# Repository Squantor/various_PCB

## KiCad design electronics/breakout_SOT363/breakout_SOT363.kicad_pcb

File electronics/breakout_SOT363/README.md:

# STO363 breakout board
Simple breakout for SOT363 devices
## TODO's
Still some things need to be done:
* Review with one night in between
* Produce at [OSHPARK](https://oshpark.com/)
* Assemble
* Test & characterise
* update Readme.md with pictures and BOM

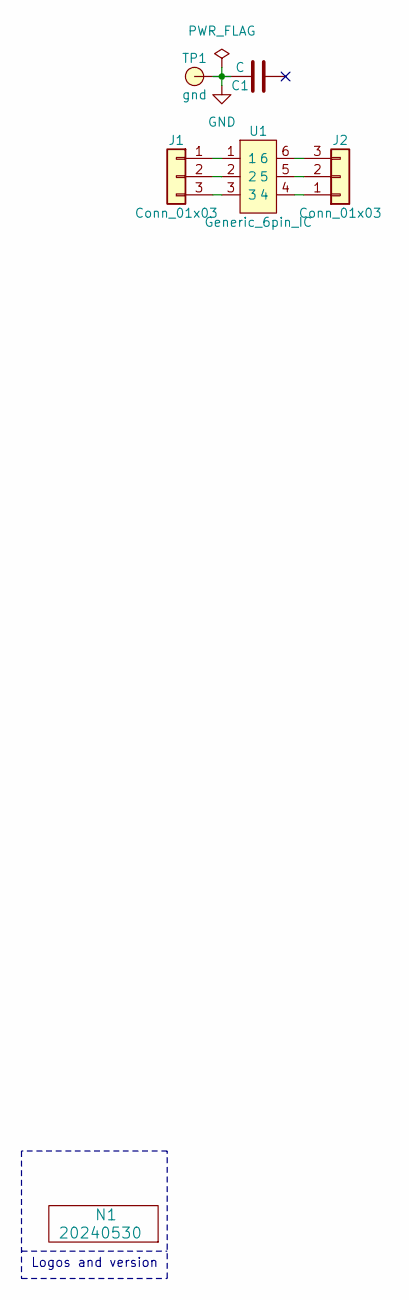
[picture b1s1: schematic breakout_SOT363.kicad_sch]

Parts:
C1: C; C_0805+0603
J1, J2: Conn_01x03; Header-0254-1X03-H010
N1: 20240530; Label_Generic
TP1: gnd; TestPoint_hole_H03R07
U1: Generic_6pin_IC; SOT363-NXP-hand

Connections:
GND: C1.1, TP1.1
unnamed: J1.1, U1.1
unnamed: J1.2, U1.2
unnamed: J1.3, U1.3
unnamed: J2.1, U1.4
unnamed: J2.2, U1.5
unnamed: J2.3, U1.6

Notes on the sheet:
Logos and version

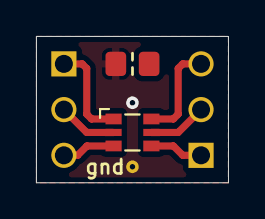
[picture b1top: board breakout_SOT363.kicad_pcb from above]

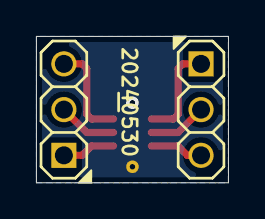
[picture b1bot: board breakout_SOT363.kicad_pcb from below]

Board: 2 copper layers, 10.7 x 8.1 mm, 6 parts (3 on the bottom side), 7 nets.

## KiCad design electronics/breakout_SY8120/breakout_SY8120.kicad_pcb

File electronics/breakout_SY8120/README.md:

# SY8120 breakout board
Breakout for the [SY8120I](https://datasheet.lcsc.com/szlcsc/2001171834_Silergy-Corp-SY8120IABC_C479076.pdf) step down converter, can also be used as a LM7805 replacement.
## TODO's
Still some things need to be done:
* Review with one night in between
* Produce at [OSHPARK](https://oshpark.com/)
* Assemble
* Test & characterise
* update Readme.md with pictures and BOM
## BOM
* [SY8120I](https://lcsc.com/product-detail/DC-DC-Converters_Silergy-Corp-SY8120IABC_C479076.html)
* [Inductor 4.7uH 3.2A](https://lcsc.com/product-detail/Inductors-SMD_TDK-SLF6045T-4R7N2R4-3PF_C93218.html)
* [Capacitor 10uF 25V X7R](https://lcsc.com/product-detail/Multilayer-Ceramic-Capacitors-MLCC-SMD-SMT_Samsung-Electro-Mechanics-CL31B106KAHNNNE_C14860.html)

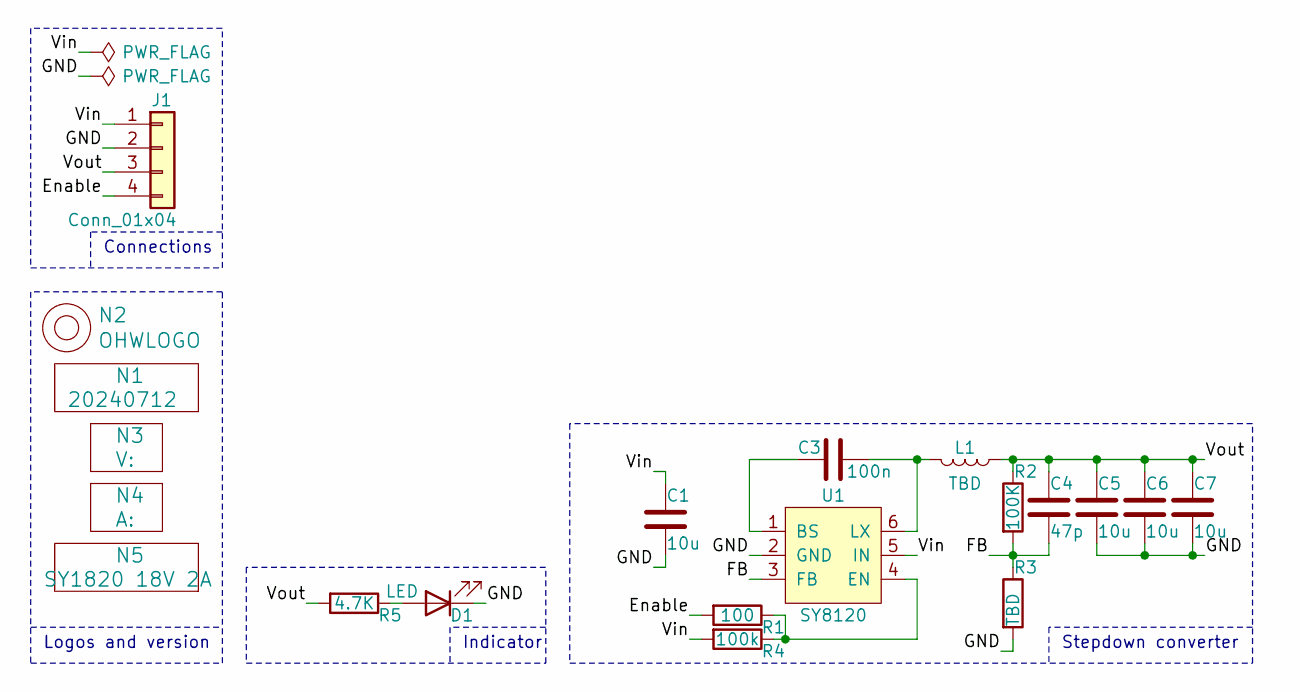
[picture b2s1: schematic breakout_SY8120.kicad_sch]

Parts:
C1: 10u; C_1206_0805
C3: 100n; C_0603
C4: 47p; C_0603
C5, C6, C7: 10u; C_0805
D1: LED; LED_0603_hand
J1: Conn_01x04; Header-0254-1X04-H010
L1: TBD; L_SLF70XX_SLF60XX_hand
N1: 20240712; Label_Generic
N2: OHWLOGO; OSHW-Symbol_6.7x6mm_SilkScreen
N3: V:; Label_Note_medium
N4: A:; Label_Note_medium
N5: SY1820 18V 2A; Label_Generic
R1: 100; R_0603_hand
R2: 100K; R_0603_hand
R3: TBD; R_0603_hand
R4: 100k; R_0603_hand
R5: 4.7K; R_0603_hand
U1: SY8120; SOT23-6-HAND

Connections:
/Enable: J1.4, R1.2
/FB: C4.2, R2.2, R3.1, U1.3 (FB)
/GND: C1.2, C5.2, C6.2, C7.2, D1.1 (K), J1.2, R3.2, U1.2 (GND)
/Vin: C1.1, J1.1, R4.2, U1.5 (IN)
/Vout: C4.1, C5.1, C6.1, C7.1, J1.3, L1.1, R2.1, R5.2
unnamed: D1.2 (A), R5.1
unnamed: C3.2, U1.1 (BS)
unnamed: R1.1, R4.1, U1.4 (EN)
unnamed: C3.1, L1.2, U1.6 (LX)

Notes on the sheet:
Connections
Stepdown converter
Logos and version
Indicator

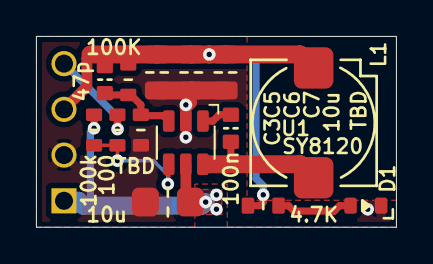
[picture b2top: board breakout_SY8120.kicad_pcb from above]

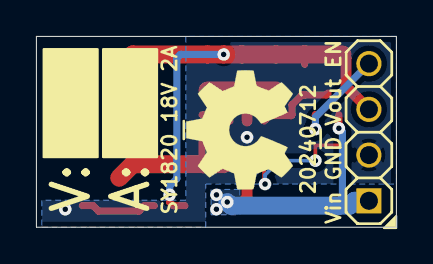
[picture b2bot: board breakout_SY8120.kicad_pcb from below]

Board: 2 copper layers, 20.0 x 10.6 mm, 20 parts (6 on the bottom side), 9 nets.
